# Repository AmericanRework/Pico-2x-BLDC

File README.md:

# Dual BLDC Controller
One RP2040 Pico drives two brushless motors! Uses SimpleFOC + Halls + TO-220 mosfets or IGBTs. Trying for low cost + lots of flexibility + solder it yourself at home + repairable. Works as a 3x DC motor controller as well.

**Features:**

RP2040 Pico running Simplefoc (https://simplefoc.com/) and using halls (or -untested but should be possible- encoders) for motor commutation. (No FOC - RP2040 doesn't have enough A/D channels for 2x motor FOC.) Current sensing: 1 A/D channel and shunt resistor per motor. Uses 2304 half-H drivers. Can assemble only half the board if you only want one servo amp / want more pico I/O's. Spot for big diodes if you want 'em - Big motors seem to eat my mosfet body diodes rather quickly and IGBT's don't have body diodes. 

Control via usb serial or hardware serial. I2C, SPI, and software CAN might work but are untested. Serial is Human readable, following the simplefoc commander schema: AE1 enables motor, A10 sets motor A to 10 rev/sec, A0 stops motor A. AE0 quickly drops power to motor a. etc... B10 sets motor B to 10 rev/sec... etc... This allows you to control, test, and modify this servo amp right from the Arduino IDE or pretty much anything with a USB port or serial port.

Boards have a spot for molex plugs that are pin compatible with Husqvarna 450x automower drive motors. (NOT the cut motor - it's a different pinout but you can re-pin the cut motor - see additionalNotes.txt) 

Board requires your motor power DC source, and ~12vdc@ say 50mA. The board can either make 3.3v for the RP2040 pico, or you can provide external 3.3v. 

There's a very simple heartbeat signal in the code - if the amp doesn't get an instruction from serial it'll shut down, or delete that line to go forever!

**Assembly/Setup:**

Boards require SMD paste soldering and normal soldering to build: 

- SMD: It's not bad, order a solder mask when you order the board, place components, toaster oven for 3 mins. All SMD components are on the same side of the board. No tiny SMD stuff like the rp2040 chip itself - that's why we use a pico. All diodes are NOT SMD so you can tell which direction they go. (I can never see the tiny lines.) 
- Normal Soldering: in particular the mosfets. They are TO-220 because you are a hacker. You can solder in mosfets you have laying around and then de-solder them yourself to put better ones in. Or put in 3x0.1" pin headers so you can just plug in mosfets when you inevitably dead short them after trying to roll your own 3 phase driver. Basically you might want to 1. swap mosfets lots as you scratch write a 3phase driver. 2. use whatever mosfets are around. 3. repair it yourself. All of these would wreck a normal board but here you can just break out your trusty soldering iron and fix this board instead of throwing it in the trash!
- Make sure you order 2oz copper board so you get thick traces and can use higher current.

Assembled board:

If you don't want to use the A/D (or want to repurpose any other inputs/outputs after you get a board) you can cut the trace to that pin(ehhh. update. not all the traces can be cut. is on hit list for next version), and there's a tinned hole for you to take over. And again, you don't have to build both servo amps if you want more IO's. 

'Firmware' for the rp2040 has some basic configuration and setup instructions in comments at the top of the code. It's pretty well tested and has been running on 2 boards for months without failing on an automower. Open up Arduino ide, install libraries: SimpleFOC, SimpleFOC drivers, and the Earle Philhower rp2040 core, compile and upload to your pico, good to go. Check top of the firmware file (RP2040SFocAmp.ino) for various additional documentation that might help you get started. 

There are two other firmware versions - one example for 3x DC motors, and one old version based on (https://github.com/ClemensElflein/xESC2040/tree/main/firmware/src) that does not use simplefoc. Both 'other' firmware versions need their pins.h file checked to be sure they follow the current board pico pin assignments, but should be somewhat functional other than that afaik. Let's call them good starting points. 

**Tested**

Tested using velocity control and torque control up to 10A/21v. You'll want heatsinks and low rdson mosfets to get to 10A. Tested the half-h drivers with igbts and better mosfets on a big inductive load to 60V, will update as we test more. Two boards are running in a Husqvarna 450x Automower as I write this. Maybe 10 hours of operation so far. Will update if/when anything fails. Update: ~100hrs of mowing, 0 servo amp faults/problems. Will still update if/when anything fails.

2 amps, 3 motors. One board has both drive motors, one has the cut motor.

Tested with 3x brushed (non 3 phase) motors using https://github.com/simplefoc/Arduino-FOC-dcmotor  - worked great but I did not test feedback, just that it could spin the motors. Off the top of my head there's only enough pico pins for 2x quadrature encoders.

**Thank you:**

Big thank you to https://github.com/ClemensElflein/ for creating the Open Mower project and his very well thought out 3 phase rp2040 servo amp code. His project inspired me to take the leap and make this happen. The original plan was use the openmower framework to control this servo amp, again - the amp plugs right into 450X automower drive motors, no hacking required. This board could(at least used to!) run (a version of?) the Xesc2040 servo amp code. Creating a firmware for this board that allows it to connect to openmower would be cool but I ended up writing a very simple mower controller instead.

SimpleFOC is absolutely brilliant. Can't recommend enough. If you are making bldc controllers they are a great place to start! (https://simplefoc.com/)

RP2040 / Pi Pico + Earle Philhower core (https://github.com/earlephilhower/arduino-pico) has been rock solid and a joy to work on. 

Thanks to everyone who open sources their work - makes the world a better place. Hope my code helps you!

**Plans/Stuff that's broken, rough order:**

- Current sense is at best not super calibrated, at worst needs work. Functions well enough to shut down the amp if current limit is hit.
- Test both DC and BLDC motors with an encoder instead of halls.
- Build more robots using this amp.
- Test it up to 240vdc/10A. Should work?
- When you disable a moving simplefoc motor with an 'AE0', it'll try to jump back to that velocity when you re-enable it. Might be fixed in newest simplefoc version or maybe it's something I did. Low priority 'cause it just spins a wheel a bit when you re-enable. Could be much a bigger problem on say a robot arm or CNC with a hard stop.
- Connect JUST the 2304's to a Mesa FPGA board running linuxCNC. Yep. Dump the pico and put your own brain on these drivers.
- I2C should work via pico pins GP17 and GP16. I think there is also now software CAN for the 2040 - loose 25% or so of one core but get CAN. Should be able to get it working. SPI is also exposed on pins 16/17/18/19 but again is untested. 

**Next board iteration:**

- Going to be a while. I've got enough of these boards for my next couple years of planned projects. Maybe...2027 or so we'll fix this stuff and anything else that shows up. Only thing that will trigger a sooner update is if high voltage or DC motor mode doesn't work.
- Heat sinks: Mosfet locations are not in a nice line. We've got 1 sink per mosfet, and once we start using more power we might want some real cooling here not just tiny heat sinks to air. Is it worth the pain of moving everything? Eh... Maybe. Might be easier to just machine the right pockets/holes into an aluminum block. 
- Delete the onboard 3.3v - Turns out you're not supposed to use linear regulators as DC-DC converters. Oops. It works but wastes 40mA+. Delete it 'cause 3.3v or 5v can come from RPi or BBB or pretty much any other board you use to drive this. AND if you have external 3.3v you can dump power to the pico even if you leave the DC main power connected.
- Redo pico io mapping so that each half-H is on it's own PWM slice.
- Motor 1 half-h cutable-traces: if you cut the top side trace between the pico and the tinned hole, remain connected to their half-h because traces went straight to the pico pins. 
- Make the power input and GND holes large enough to accommodate 12Ga wire.
- Fix various labels on the board. FID2 looking at you. Also most of the Motor 2 labels.

Cheers!
-American Rework

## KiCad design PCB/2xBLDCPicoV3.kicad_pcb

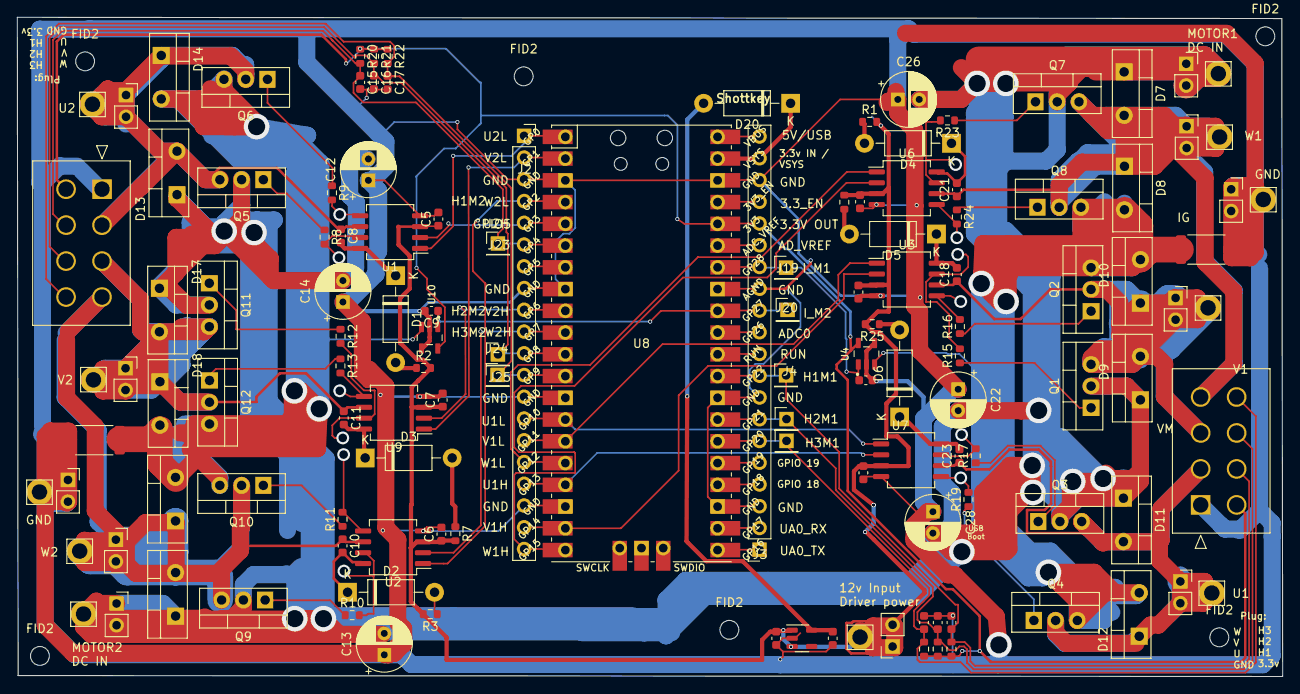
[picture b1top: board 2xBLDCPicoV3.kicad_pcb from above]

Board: 4 copper layers, 147.8 x 77.0 mm, 124 parts (0 on the bottom side), 88 nets.

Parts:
C1, C5, C6, C7, C19, C27: 100nF; C_0603_1608Metric
C2, C3, C4, C9, C15, C16, C17, C20: .1uF; C_0603_1608Metric
C8, C10, C11, C18, C21, C23: 470nF/16V; C_0603_1608Metric
C12, C26: 2.2uF/400V; CP_Radial_D6.3mm_P2.50mm
C13, C14, C22, C28: 2.2uF/400v; CP_Radial_D6.3mm_P2.50mm
C24, C25: 10uF/16V; C_0603_1608Metric
D1, D2, D3, D4, D5, D6: UF4007; D_DO-41_SOD81_P10.16mm_Horizontal
D7, D8, D9, D10, D11, D12, D13, D14, D15, D16, D17, D18: C3D10060A; TO-220-2_Vertical
D20: 1N5817; D_DO-41_SOD81_P10.16mm_Horizontal
FID2, FID2#2, FID2#3, FID2#4, FID2#5, FID2#6: MTG Hole; MountingHole_2.2mm_M2
J1, J22: 874270842; CON_874270842
J2, J3: Conn_01x20_Pin; PinSocket_1x20_P2.54mm_Vertical
J4, J5, J7, J19, J20, J23, J24, J25: Conn_01x01_Pin; PinHeader_1x01_P2.54mm_Vertical
J6, J8, J9, J10, J11, J12, J13, J15, J16, J17, J18: Conn_01x02; PinSocket_1x02_P2.54mm_Vertical
Q1, Q2, Q3, Q4, Q5, Q6, Q11, Q12: IRF540N; TO-220-3_Vertical
Q7, Q8, Q9, Q10: STGP10NC60H; TO-220-3_Vertical
R1, R2, R3, R7, R8, R9, R10, R11, R12, R13, R15, R16, R17, R19, R23, R24, R25, R26: 010; R_0603_1608Metric
R4, R5, R6, R20, R21, R22: 2k2; R_0603_1608Metric
R14, R18: 1mR; R_2512_6332Metric
U1, U2, U3, U6, U7, U9: IRS2304; SO-8_5.3x6.2mm_P1.27mm
U4, U10: INA180A4; SOT95P280X145-5N
U5: XC6220B331MR; SOT-23-5
U8: Pico; RPi_Pico_SMD_TH

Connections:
+3V3: C25.1, D20.2 (A), U5.5 (VOUT)
+12V: C1.1, C5.1, C6.1, C7.1, C19.1, C24.1, C27.1, J11.1, J11.2, R1.2, R2.2, R3.2, R7.2, R25.2, R26.2, U1.3 (VCC), U2.3 (VCC), U3.3 (VCC), U5.1 (VIN), U5.3 (CE), U6.3 (VCC), U7.3 (VCC), U9.3 (VCC)
/+3.3V to Sensors: J1.5, J22.5, R4.1, R5.1, R6.1, R20.1, R21.1, R22.1
/HALL1: C2.1, J1.6, J4.1, R4.2
/HALL1M2: C15.1, J22.6, J23.1, R20.2
/HALL2: C3.1, J1.7, J5.1, R5.2
/HALL2M2: C16.1, J22.7, J24.1, R21.2
/HALL3: C4.1, J1.8, J7.1, R6.2
/HALL3M2: C17.1, J22.8, J25.1, R22.2
/MCU/+3.3V to Sensors: J3.16, U8.36 (3V3)
/MCU/ADCINSPARE1: J3.11, U8.31 (GPIO26_ADC0)
/MCU/CURRENT_SENSE: C20.1, J3.14, J19.1, U4.1 (OUT), U8.34 (GPIO28_ADC2)
/MCU/CURRENT_SENSEM2: C9.1, J3.12, J20.1, U8.32 (GPIO27_ADC1), U10.1 (OUT)
/MCU/HALL_1: J3.9, U8.29 (GPIO22)
/MCU/HALL_2: J3.7, U8.27 (GPIO21)
/MCU/HALL_2M2: J2.11, U8.11 (GPIO8)
/MCU/HALL_3: J3.6, U8.26 (GPIO20)
/MCU/HALL_3M2: J2.12, U8.12 (GPIO9)
/MCU/Hall_1_M2 / i2c0 SDA / UART1_TX: J2.6, U8.6 (GPIO4)
/MCU/Spare1/spi0 TX/i2c1 SCL: J3.5, U8.25 (GPIO19)
/MCU/Spare2/spi0 SCK/i2c1 SDA: J3.4, U8.24 (GPIO18)
/MCU/Spare3 / i2c0 SCL UART1_RX: J2.7, U8.7 (GPIO5)
/MCU/U1H: J2.17, U7.2 (HIN), U8.17 (GPIO13)
/MCU/U1L: J2.14, U7.1 (LIN), U8.14 (GPIO10)
/MCU/U2H: J2.5, U1.2 (HIN), U8.5 (GPIO3)
/MCU/U2L: J2.1, U1.1 (LIN), U8.1 (GPIO0)
/MCU/UART0_RX /spi0 Csn / I2C0 SCL: J3.2, U8.22 (GPIO17)
/MCU/UART0_TX /spi0 RX / I2C0 SDA: J3.1, U8.21 (GPIO16)
/MCU/V1H: J2.19, U3.2 (HIN), U8.19 (GPIO14)
/MCU/V1L: J2.15, U3.1 (LIN), U8.15 (GPIO11)
/MCU/V2H: J2.9, U8.9 (GPIO6), U9.2 (HIN)
/MCU/V2L: J2.2, U8.2 (GPIO1), U9.1 (LIN)
/MCU/W1H: J2.20, U6.2 (HIN), U8.20 (GPIO15)
/MCU/W1L: J2.16, U6.1 (LIN), U8.16 (GPIO12)
/MCU/W2H: J2.10, U2.2 (HIN), U8.10 (GPIO7)
/MCU/W2L: J2.4, U2.1 (LIN), U8.4 (GPIO2)
/PowerM1/HSW: R23.2, U6.7 (HO)
/PowerM1/IGBT_GND: D8.2 (A), D10.2 (A), D12.2 (A), Q2.3 (S), Q4.3 (S), Q8.3 (S), R18.1, U4.3 (IN+)
/PowerM1/LSW: R24.2, U6.5 (LO)
/PowerM2/HSW: R10.2, U2.7 (HO)
/PowerM2/IGBT_GND: D14.2 (A), D16.2 (A), D18.2 (A), Q6.3 (S), Q10.3 (S), Q12.3 (S), R14.1, U10.3 (IN+)
/PowerM2/LSW: R11.2, U2.5 (LO)
/PowerM2/U_To_PlugM2: C8.1, D13.2 (A), D14.1 (K), J18.1, J18.2, Q5.3 (S), Q6.2 (D), U1.6 (VS)
/PowerM2/VM2: C12.2, C13.2, C14.2, D13.1 (K), D15.1 (K), D17.1 (K), J15.1, J15.2, Q5.2 (D), Q9.2 (D), Q11.2 (D)
/PowerM2/V_To_PlugM2: C11.1, D17.2 (A), D18.1 (K), J17.1, J17.2, Q11.3 (S), Q12.2 (D), U9.6 (VS)
/PowerM2/W_To_PlugM2: C10.1, D15.2 (A), D16.1 (K), J16.1, J16.2, Q9.3 (S), Q10.2 (D), U2.6 (VS)
/U_To_Plug: C23.1, D11.2 (A), D12.1 (K), J1.2, J9.1, J9.2, Q3.3 (S), Q4.2 (D), U7.6 (VS)
/VM: C22.2, C26.2, C28.2, D7.1 (K), D9.1 (K), D11.1 (K), J10.1, J10.2, Q1.2 (D), Q3.2 (D), Q7.2 (D)
/V_To_Plug: C18.1, D9.2 (A), D10.1 (K), J1.3, J6.1, J6.2, Q1.3 (S), Q2.2 (D), U3.6 (VS)
/W_To_Plug: C21.1, D7.2 (A), D8.1 (K), J1.4, J8.1, J8.2, Q7.3 (S), Q8.2 (D), U6.6 (VS)
GND: C1.2, C2.2, C3.2, C4.2, C5.2, C6.2, C7.2, C9.2, C12.1, C13.1, C14.1, C15.2, C16.2, C17.2, C19.2, C20.2, C22.1, C24.2, C25.2, C26.1, C27.2, C28.1, J1.1, J2.3, J2.8, J2.13, J2.18, J3.3, J3.8, J3.13, J3.18, J12.1, J12.2, J13.1, J13.2, J22.1, R14.2, R18.2, U1.4 (COM), U2.4 (COM), U3.4 (COM), U4.2 (GND), U4.4 (IN-), U5.2 (GND), U6.4 (COM), U7.4 (COM), U8.3 (GND), U8.8 (GND), U8.13 (GND), U8.18 (GND), U8.23 (GND), U8.28 (GND), U8.33 (AGND), U8.38 (GND), U9.4 (COM), U10.2 (GND), U10.4 (IN-)
unnamed: D1.2 (A), R2.1
unnamed: C8.2, D1.1 (K), U1.8 (VB)
unnamed: D2.2 (A), R3.1
unnamed: C10.2, D2.1 (K), U2.8 (VB)
unnamed: D3.2 (A), R7.1
unnamed: C11.2, D3.1 (K), U9.8 (VB)
unnamed: D4.2 (A), R1.1
unnamed: C21.2, D4.1 (K), U6.8 (VB)
unnamed: D5.2 (A), R26.1
unnamed: C18.2, D5.1 (K), U3.8 (VB)
unnamed: D6.2 (A), R25.1
unnamed: C23.2, D6.1 (K), U7.8 (VB)
unnamed: D20.1 (K), J3.19, U8.39 (VSYS)
unnamed: J3.10, U8.30 (RUN)
unnamed: J3.15, U8.35 (ADC_VREF)
unnamed: J3.17, U8.37 (3V3_EN)
unnamed: J3.20, U8.40 (VBUS)
unnamed: Q1.1 (G), R15.1
unnamed: Q2.1 (G), R16.1
unnamed: Q3.1 (G), R17.1
unnamed: Q4.1 (G), R19.1
unnamed: Q5.1 (G), R8.1
unnamed: Q6.1 (G), R9.1
unnamed: Q7.1 (G), R23.1
unnamed: Q8.1 (G), R24.1
unnamed: Q9.1 (G), R10.1
unnamed: Q10.1 (G), R11.1
unnamed: Q11.1 (G), R12.1
unnamed: Q12.1 (G), R13.1
unnamed: R8.2, U1.7 (HO)
unnamed: R9.2, U1.5 (LO)
unnamed: R15.2, U3.7 (HO)
unnamed: R16.2, U3.5 (LO)
unnamed: R17.2, U7.7 (HO)
unnamed: R19.2, U7.5 (LO)
unnamed: R12.2, U9.7 (HO)
unnamed: R13.2, U9.5 (LO)

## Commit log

2024-04-04 Rename RP2040SFocAmp.ino to Firmware/RP2040SFocAmp.ino
2024-04-04 Rename pins.h to Firmware/pins.h
2024-04-04 Picture of amp + Husqvarna mower motor
2024-04-04 Rename DualBLDCController.jpg to AssembledDualBLDCController.jpg
2024-04-04 Delete AssembledDualBLDCController.jpg
    Holy F*** If you can't make a web interface why would I let you install a script on my machine? And if you made a web interface that worked, I wouldn't need a script in the first place!
2024-04-04 BOM done! Crossed off todo list.
2024-05-05 qty was wrong
